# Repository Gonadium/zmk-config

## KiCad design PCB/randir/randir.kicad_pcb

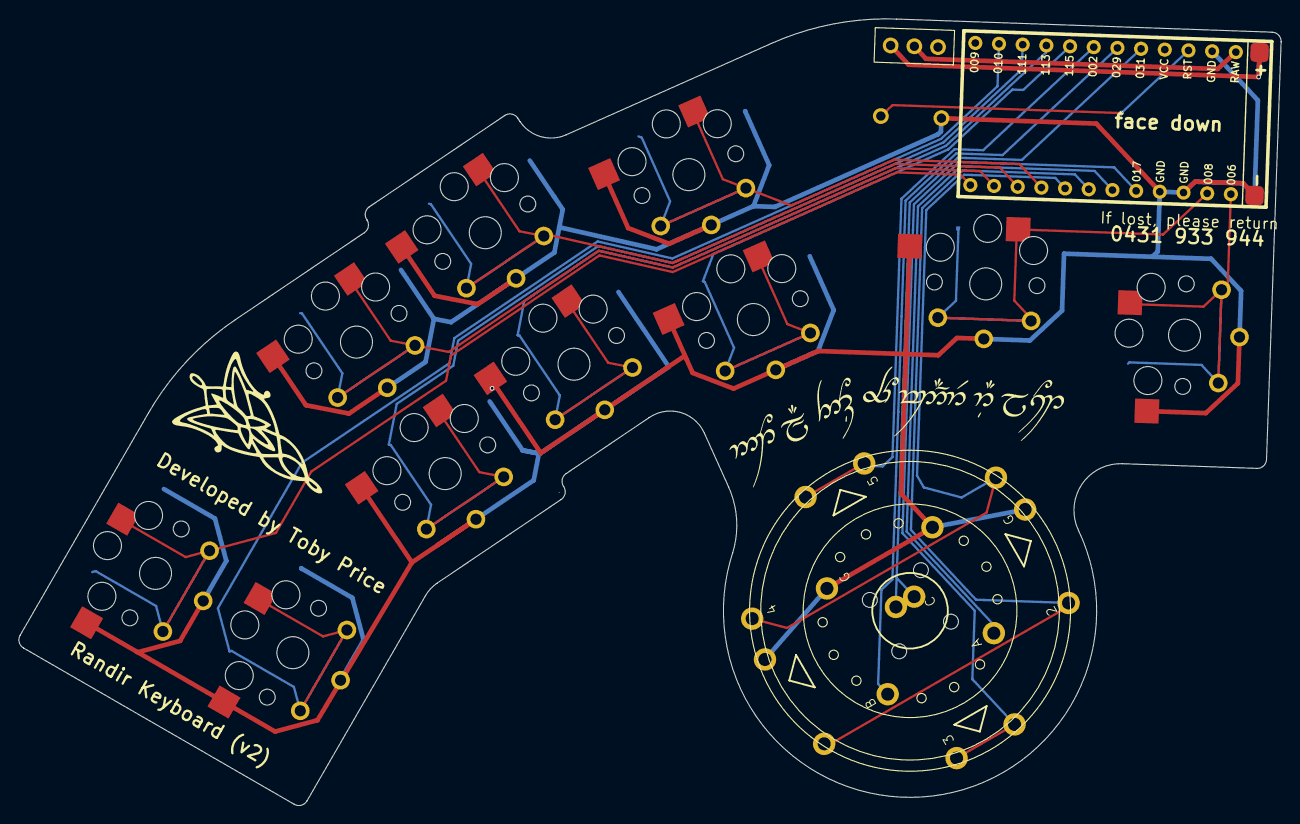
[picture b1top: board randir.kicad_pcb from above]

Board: 2 copper layers, 135.3 x 84.3 mm, 11 parts (1 on the bottom side), 11 nets.

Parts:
SW1, SW1#2, SW5, SW10: SW_Push; pg1350-rev-hs-1.25U
SW2, SW3, SW4, SW7, SW8, SW9: SW_Push; pg1350-rev-hs-1U
U1: nice_nano_Toby

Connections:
D0: SW10.1, U1.0
D1: SW5.1, U1.1
D6: SW4.1, U1.6
D7: SW3.1, U1.7
D8: SW2.1, U1.8
D9: SW1.1, U1.9
D14: SW7.1, U1.14
D15: SW8.1, U1.15
D16: SW1#2.1, U1.16
D18: SW9.1, U1.18
GND: SW1.2, SW1#2.2, SW2.2, SW3.2, SW4.2, SW5.2, SW7.2, SW8.2, SW9.2, SW10.2, U1.Bat- (1), U1.GND

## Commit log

2023-04-11 Initial User Config.
2023-04-12 errors
2023-04-12 corrected promicro pinouts
2023-04-16 Fyisnifni
2023-04-20 bm v
2023-04-20 Revert "Update randir.keymap"
    This reverts commit 06bf42b83408f90a55e4f1ecf1fab337b280eb99.
2023-04-20 THIS IS WORKING (but no JS)
    sfd
2023-04-20 xvzc
2023-04-21 lets get a compile
2023-04-21 WORKING
2023-04-21 Sleep on
    Enabled CONFIG_ZMK_SLEEP=y
    from conf
2023-04-21 Enabled TX PWR
    enabled CONFIG_BT_CTLR_TX_PWR_PLUS_8=y from conf
2023-04-21 Enabled Joystick
    enabled CONFIG_JOY=y from conf
2023-04-21 Changed to CodeAndrew PR
    Changed the PR to mousepr-andrew in west.yml
2023-04-21 Enabled CONFIG_ZMK_MOUSE
    enabled CONFIG_ZMK_MOUSE=y from conf
2023-04-21 removed CodeAndrew PR
    Can't seem to get this to work.
    removed PR from west.yml
    removed joystick from conf
2023-04-21 WORKING AGAIN
2023-04-21 enable CONFIG_ZMK_MOUSE
    Enabled CONFIG_ZMK_MOUSE=y
    from conf
2023-04-21 removed Combo Settings from shield
    Removed
    CONFIG_ZMK_COMBO_MAX_PRESSED_COMBOS=1
    CONFIG_ZMK_COMBO_MAX_COMBOS_PER_KEY=127
    CONFIG_ZMK_COMBO_MAX_KEYS_PER_COMBO=10
    from Kconfig.shield
2023-04-21 Remove ZMK Mouse
2023-04-21 Changed combo settings
2023-04-21 Changed combo settings again
2023-04-21 WORKING BUILD
2023-04-21 start changing to PR
    Including codeandrew remote
2023-04-21 MousePR-Codeandrew
    Try this PR Build
2023-04-21 try joystick PR
2023-04-21 Back to working
2023-04-21 Try tewtham - Dactyl_Typsesafe PR
    https://github.com/tewtham/zmk/tree/dactyl_typesafe
2023-04-21 Try Tewtham again
2023-04-21 Add joystick and ADC to defconfig
2023-04-21 try again
2023-04-21 test
    test
2023-04-21 cvbf
2023-04-21 test
2023-04-21 Is andrecode working?
2023-04-21 Retry MousePR
2023-04-21 Add Joystick configs
    add CONFIG_JOYSTICK=y to conf
    add config JOYSTICK
    default y to defconfig
2023-04-21 get it working again
2023-04-21 Add JS in Conf
2023-04-21 add js in defconfig
2023-04-21 Get it working again
    It seems that adding the Joystick config anywhere will break this
2023-04-21 Add JS to CodeAndrew's Main PR
2023-05-11 hfxg
2023-05-13 Macro update
2023-05-16 sides
2023-07-08 sdf
    dsf
